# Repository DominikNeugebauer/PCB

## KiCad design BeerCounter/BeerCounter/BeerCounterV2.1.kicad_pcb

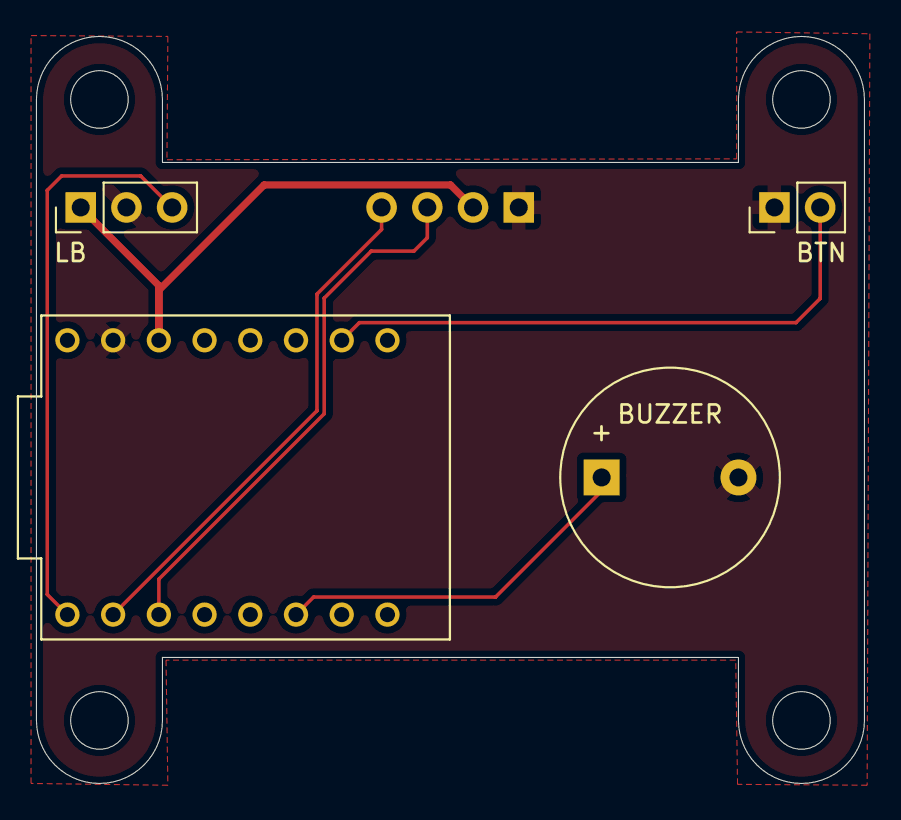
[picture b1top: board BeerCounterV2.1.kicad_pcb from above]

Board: 2 copper layers, 46.0 x 41.5 mm, 5 parts (1 on the bottom side), 7 nets.

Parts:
BTN: Conn_01x02; PinHeader_1x02_P2.54mm_Vertical
BUZZER: Buzzer; Buzzer_12x9.5RM7.6
DISPLAY: Conn_01x04; PinHeader_1x04_P2.54mm_Vertical
LB: Conn_01x03; PinHeader_1x03_P2.54mm_Vertical
U1: ESP32-C3_SUPERMINI_TH; MODULE_ESP32-C3_SUPERMINI_TH

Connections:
3V3: DISPLAY.2, LB.1, U1.3.3 (3V3)
BTN: BTN.2, U1.1 (GPIO1)
BUZZER: BUZZER.1 (+), U1.10 (GPIO10)
GND: BTN.1, BUZZER.2 (-), DISPLAY.1, LB.2, U1.G (GND)
LIGHT_BARRIER: LB.3, U1.5 (GPIO5)
SCL: DISPLAY.3, U1.7 (GPIO7)
SDA: DISPLAY.4, U1.6 (GPIO6)
